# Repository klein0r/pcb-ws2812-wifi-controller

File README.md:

# WS2812 / SK6812 Wifi Controller Custom PCB

Control your addressable LED with custom software like [WLED](https://github.com/Aircoookie/WLED)

[Gerber-Files](https://github.com/klein0r/pcb-ws2812-wifi-controller/releases)

## Preview

## Components

- C1, C2: Capacitor 0805 100nF
- C3: Capacitor Radial 3.8mm 1000μF 6.3
- F1: Stelvio Kontek STV PTF/75 + Fuse 5x20mm, 5A (max. 6A)
- J1: PHC 1725672 - MPT 0,5 / 4-2,54
- J2: 1x5 2.54mm Male Pin Headers (for flashing - soldering not required)
- J3: PHC 1725669 - MPT 0,5 / 3-2,54
- R1, R2, R3, R4, R5: Resistor 0805 10k
- R6: Resistor 0805 330
- SW1, SW2: Push Button 3*6*2.5mm
- U1: AMS1117-3.3 SOT 223
- U2: ESP-12F
- U3: SN74AHCT125DR

## GPIO

- GPIO4 = Data line of addressable strip

## Cases

- [Case by DrNuke33](https://www.thingiverse.com/thing:4909109)

## Older Versions

*See git tag / releases*

**0.1**

**0.2**

**0.3**

**0.4**

## License

The MIT License (MIT)

Copyright (c) 2026 Matthias Kleine <info@haus-automatisierung.com>

Permission is hereby granted, free of charge, to any person obtaining a copy
of this software and associated documentation files (the "Software"), to deal
in the Software without restriction, including without limitation the rights
to use, copy, modify, merge, publish, distribute, sublicense, and/or sell
copies of the Software, and to permit persons to whom the Software is
furnished to do so, subject to the following conditions:

The above copyright notice and this permission notice shall be included in
all copies or substantial portions of the Software.

THE SOFTWARE IS PROVIDED "AS IS", WITHOUT WARRANTY OF ANY KIND, EXPRESS OR
IMPLIED, INCLUDING BUT NOT LIMITED TO THE WARRANTIES OF MERCHANTABILITY,
FITNESS FOR A PARTICULAR PURPOSE AND NONINFRINGEMENT. IN NO EVENT SHALL THE
AUTHORS OR COPYRIGHT HOLDERS BE LIABLE FOR ANY CLAIM, DAMAGES OR OTHER
LIABILITY, WHETHER IN AN ACTION OF CONTRACT, TORT OR OTHERWISE, ARISING FROM,
OUT OF OR IN CONNECTION WITH THE SOFTWARE OR THE USE OR OTHER DEALINGS IN
THE SOFTWARE.

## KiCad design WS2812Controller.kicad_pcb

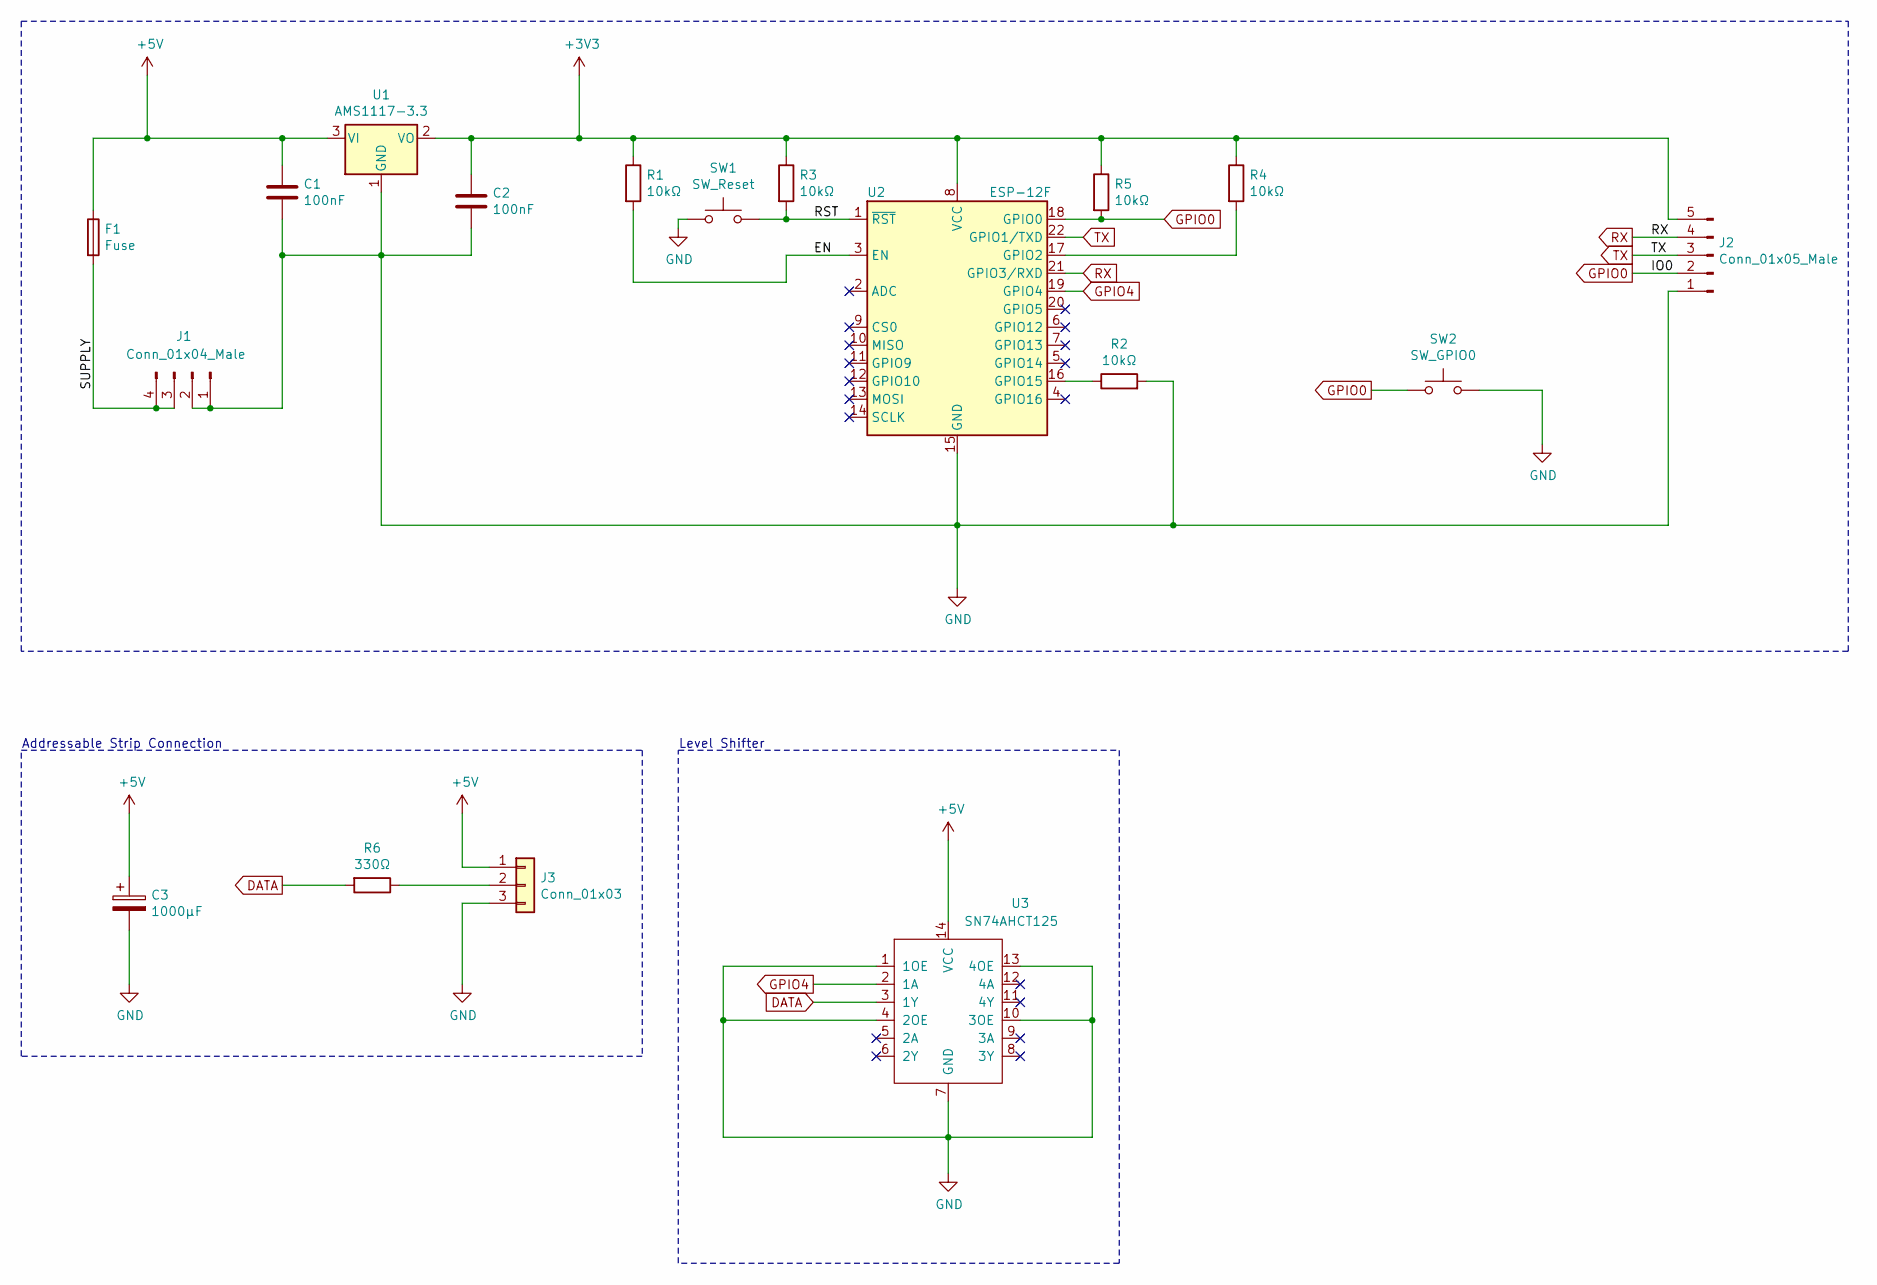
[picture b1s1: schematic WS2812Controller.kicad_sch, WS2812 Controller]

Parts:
C1, C2: 100nF; C_0805_2012Metric_Pad1.15x1.40mm_HandSolder
C3: 1000µF; CP_Radial_D8.0mm_P3.80mm
F1: Fuse; Fuse-PTF75_Stelvio
J1: Conn_01x04_Male; TerminalBlock_Phoenix_MPT-0,5-4-2.54_1x04_P2.54mm_Horizontal
J2: Conn_01x05_Male; PinHeader_1x05_P2.54mm_Vertical
J3: Conn_01x03; TerminalBlock_Phoenix_MPT-0,5-3-2.54_1x03_P2.54mm_Horizontal
R1, R2, R3, R4, R5: 10kΩ; R_0805_2012Metric_Pad1.15x1.40mm_HandSolder
R6: 330Ω; R_0805_2012Metric_Pad1.15x1.40mm_HandSolder
SW1: SW_Reset; SW_SPST_CK_RS282G05A3
SW2: SW_GPIO0; SW_SPST_CK_RS282G05A3
U1: AMS1117-3.3; SOT-223-3_TabPin2
U2: ESP-12F; ESP-12E
U3: SN74AHCT125; SN74AHCT125D

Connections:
+3V3: C2.1, J2.5, R1.1, R3.1, R4.1, R5.1, U1.2 (VO), U2.8 (VCC)
+5V: C1.1, C3.1, F1.1, J3.1, U1.3 (VI), U3.14 (VCC)
/EN: R1.2, U2.3 (EN)
/RST: R3.2, SW1.2, U2.1 (~RST)
/SUPPLY: F1.2, J1.3, J1.4
DATA: R6.2, U3.3 (1Y)
GND: C1.2, C2.2, C3.2, J1.1, J1.2, J2.1, J3.3, R2.2, SW1.1, SW2.2, U1.1 (GND), U2.15 (GND), U3.1 (1OE), U3.4 (2OE), U3.7 (GND), U3.10 (3OE), U3.13 (4OE)
GPIO0: J2.2, R5.2, SW2.1, U2.18 (GPIO0)
GPIO4: U2.19 (GPIO4), U3.2 (1A)
unnamed: J3.2, R6.1
unnamed: R2.1, U2.16 (GPIO15)
unnamed: R4.2, U2.17 (GPIO2)
RX: J2.4, U2.21 (GPIO3/RXD)
TX: J2.3, U2.22 (GPIO1/TXD)

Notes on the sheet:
Addressable Strip Connection
Level Shifter

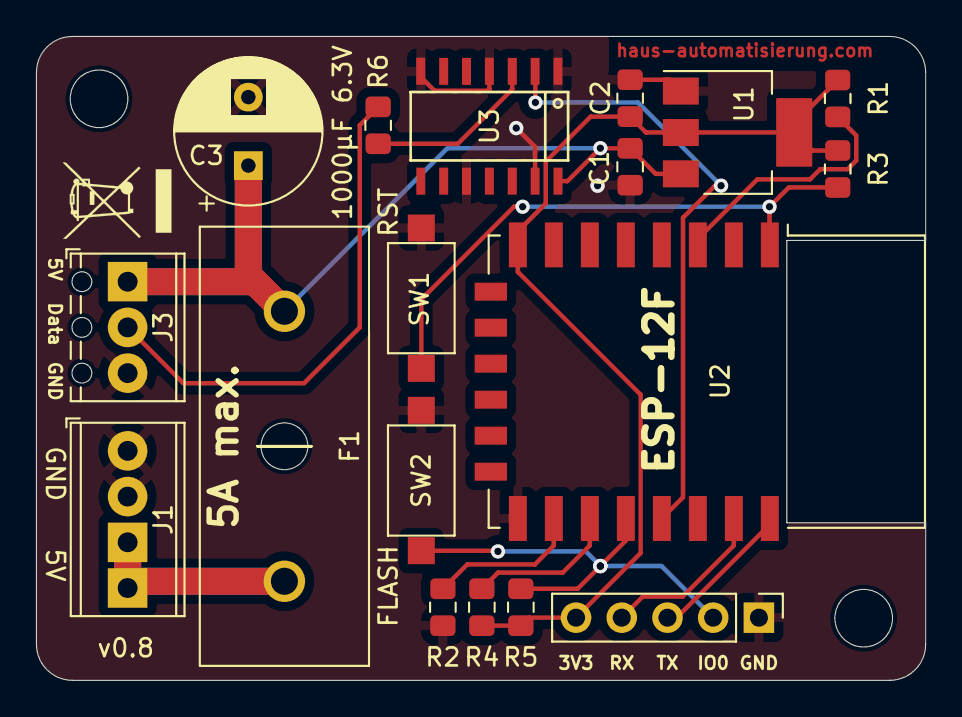
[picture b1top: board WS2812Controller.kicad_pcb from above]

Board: 2 copper layers, 49.4 x 35.8 mm, 18 parts (0 on the bottom side), 14 nets.

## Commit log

2019-12-13 Initial version
2019-12-13 Preview and Readme
2021-05-07 2019 -> 2021
2021-05-08 New layout
2021-05-08 Rounded edge cuts
2021-05-08 Readme and Preview
2021-05-08 Measurements
2021-05-11 v0.2
2021-05-12 v0.3
2021-06-10 Readme
2021-06-21 Bigger tracks for 5V supply
2021-09-29 v0.4
2021-09-29 Preview
2021-09-29 v0.5
2021-10-13 Preview Photo
2022-01-30 Update LICENSE
2022-01-30 Updated to KiCad 6
2022-01-30 Fixed minor connection issues
2022-01-30 Updated gitignore
2023-08-16 Updated preview
2023-08-16 2023
2024-05-07 v0.7
2024-05-17 Add 3d print box models
2024-07-26 2024
2026-01-28 Year 2026
